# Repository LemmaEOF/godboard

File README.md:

# Godboard

*a hypothetical custom keyboard for Projekt GODHAND*

I mostly made this as practice for designing circuit boards; I don't really expect this to actually be
a feasible controller for the game (since it's not even out yet oops)

Upper left four keys are ASDF, upper right four keys are JKL;, each set of lower four are arrow keys, and
the button in the very center is Escape. Key lighting is intended to be blue on the left side and red on
the right side to match with Godhand's UI, with the Escape key set to green.

It's designed to have reverse-mount RGBLEDs on the south side of each key (probably SK6812MINI-E), and a
Pro Micro-compatible of your choice on a socket in the center.

I assume no liability for any damage this controller undertakes while being used for Projekt GODHAND.

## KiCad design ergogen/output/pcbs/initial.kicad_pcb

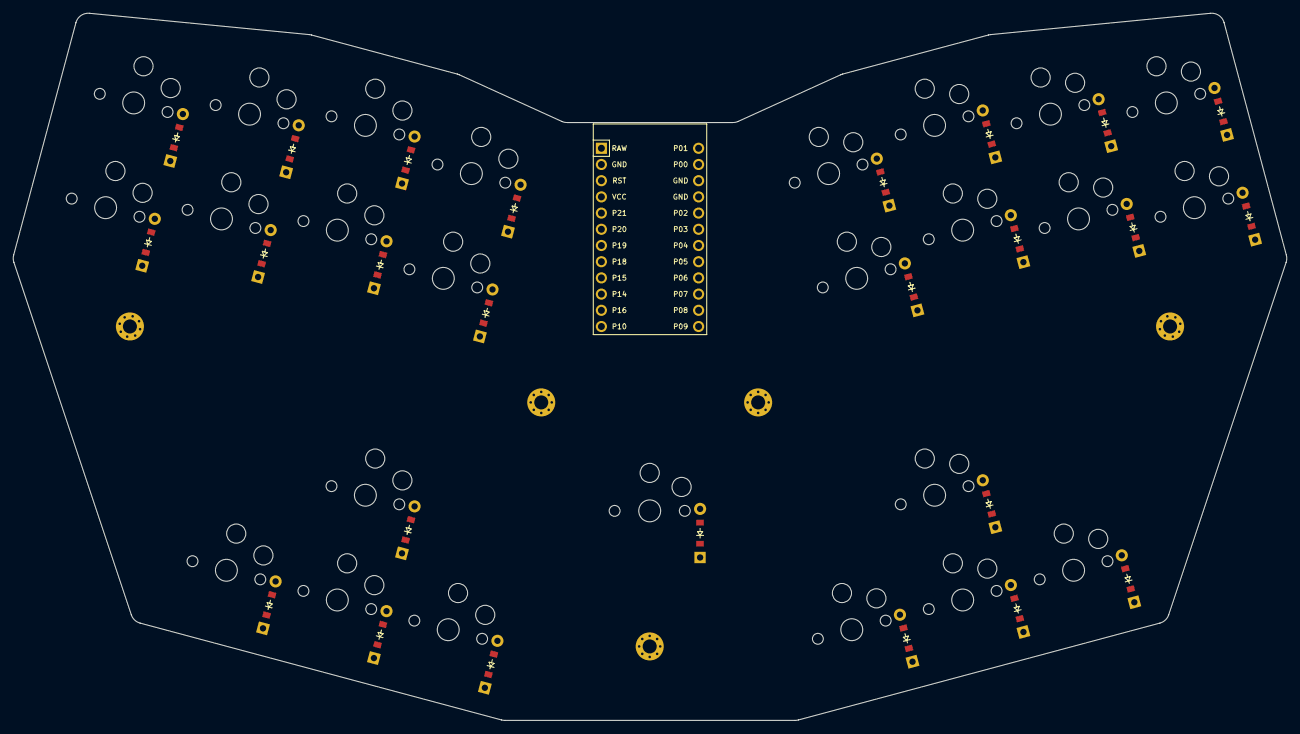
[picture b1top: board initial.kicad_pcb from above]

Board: 2 copper layers, 199.6 x 110.8 mm, 81 parts (0 on the bottom side), 39 nets, no tracks yet.

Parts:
D1, D2, D3, D4, D5, D6, D7, D8, D9, D10, D11, D12, D13, D14, D15, D16, D17, D18, D19, D20, D21, D22, D23, D24, D25: ComboDiode
LED1, LED2, LED3, LED4, LED5, LED6, LED7, LED8, LED9, LED10, LED11, LED12, LED13, LED14, LED15, LED16, LED17, LED18, LED19, LED20, LED21, LED22, LED23, LED24, LED25: WS2812B
MCU1: ProMicro
S1, S2, S3, S4, S5, S6, S7, S8, S9, S10, S11, S12, S13, S14, S15, S16, S17, S18, S19, S20, S21, S22, S23, S24, S25: PG1350
_1, _2, _3, _4, _5: MountingHole_2.2mm_M2_Pad_Via

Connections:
GND: LED1.3, LED1.33, LED2.3, LED2.33, LED3.3, LED3.33, LED4.3, LED4.33, LED5.3, LED5.33, LED6.3, LED6.33, LED7.3, LED7.33, LED8.3, LED8.33, LED9.3, LED9.33, LED10.3, LED10.33, LED11.3, LED11.33, LED12.3, LED12.33, LED13.3, LED13.33, LED14.3, LED14.33, LED15.3, LED15.33, LED16.3, LED16.33, LED17.3, LED17.33, LED18.3, LED18.33, LED19.3, LED19.33, LED20.3, LED20.33, LED21.3, LED21.33, LED22.3, LED22.33, LED23.3, LED23.33, LED24.3, LED24.33, LED25.3, LED25.33, MCU1.2, MCU1.15, MCU1.16
P4: D14.1, D16.1, D18.1, D20.1, MCU1.19
P5: MCU1.20, S5.1, S6.1, S12.1, S18.1, S19.1, S25.1
P6: D15.1, D17.1, D19.1, D21.1, MCU1.21
P7: MCU1.22, S7.1, S8.1, S13.1, S20.1, S21.1
P8: D11.1, D13.1, D24.1, MCU1.23
P9: D22.1, D23.1, D25.1, MCU1.24
P10: D9.1, D10.1, D12.1, MCU1.12
P14: LED1.2, LED1.4, LED1.22, LED1.44, LED2.2, LED2.4, LED2.22, LED2.44, LED3.2, LED3.4, LED3.22, LED3.44, LED4.2, LED4.4, LED4.22, LED4.44, LED5.2, LED5.4, LED5.22, LED5.44, LED6.2, LED6.4, LED6.22, LED6.44, LED7.2, LED7.4, LED7.22, LED7.44, LED8.2, LED8.4, LED8.22, LED8.44, LED9.2, LED9.4, LED9.22, LED9.44, LED10.2, LED10.4, LED10.22, LED10.44, LED11.2, LED11.4, LED11.22, LED11.44, LED12.2, LED12.4, LED12.22, LED12.44, LED13.2, LED13.4, LED13.22, LED13.44, LED14.2, LED14.4, LED14.22, LED14.44, LED15.2, LED15.4, LED15.22, LED15.44, LED16.2, LED16.4, LED16.22, LED16.44, LED17.2, LED17.4, LED17.22, LED17.44, LED18.2, LED18.4, LED18.22, LED18.44, LED19.2, LED19.4, LED19.22, LED19.44, LED20.2, LED20.4, LED20.22, LED20.44, LED21.2, LED21.4, LED21.22, LED21.44, LED22.2, LED22.4, LED22.22, LED22.44, LED23.2, LED23.4, LED23.22, LED23.44, LED24.2, LED24.4, LED24.22, LED24.44, LED25.2, LED25.4, LED25.22, LED25.44, MCU1.10
P15: MCU1.9, S3.1, S4.1, S10.1, S11.1, S16.1, S17.1, S23.1, S24.1
P16: D2.1, D4.1, D6.1, D8.1, MCU1.11
P18: MCU1.8, S1.1, S2.1, S9.1, S14.1, S15.1, S22.1
P19: D1.1, D3.1, D5.1, D7.1, MCU1.7
VCC: LED1.1, LED1.11, LED2.1, LED2.11, LED3.1, LED3.11, LED4.1, LED4.11, LED5.1, LED5.11, LED6.1, LED6.11, LED7.1, LED7.11, LED8.1, LED8.11, LED9.1, LED9.11, LED10.1, LED10.11, LED11.1, LED11.11, LED12.1, LED12.11, LED13.1, LED13.11, LED14.1, LED14.11, LED15.1, LED15.11, LED16.1, LED16.11, LED17.1, LED17.11, LED18.1, LED18.11, LED19.1, LED19.11, LED20.1, LED20.11, LED21.1, LED21.11, LED22.1, LED22.11, LED23.1, LED23.11, LED24.1, LED24.11, LED25.1, LED25.11, MCU1.4
far_thumb: D12.2, S12.2
home_thumb: D10.2, S10.2
home_top: D11.2, S11.2
index_bottom: D7.2, S7.2
index_home: D8.2, S8.2
main_default: D13.2, S13.2
middle_bottom: D5.2, S5.2
middle_home: D6.2, S6.2
mirror_far_thumb: D25.2, S25.2
mirror_home_thumb: D23.2, S23.2
mirror_home_top: D24.2, S24.2
mirror_index_bottom: D20.2, S20.2
mirror_index_home: D21.2, S21.2
mirror_middle_bottom: D18.2, S18.2
mirror_middle_home: D19.2, S19.2
mirror_near_thumb: D22.2, S22.2
mirror_pinky_bottom: D14.2, S14.2
mirror_pinky_home: D15.2, S15.2
mirror_ring_bottom: D16.2, S16.2
mirror_ring_home: D17.2, S17.2
near_thumb: D9.2, S9.2
pinky_bottom: D1.2, S1.2
pinky_home: D2.2, S2.2
ring_bottom: D3.2, S3.2
ring_home: D4.2, S4.2

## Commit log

2025-02-25 yknow what eight keys
